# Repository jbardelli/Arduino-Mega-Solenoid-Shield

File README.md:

# Arduino-Mega-Solenoid-Shield
Kicad files for a solenoid valve driver shield compatible with Arduino Mega

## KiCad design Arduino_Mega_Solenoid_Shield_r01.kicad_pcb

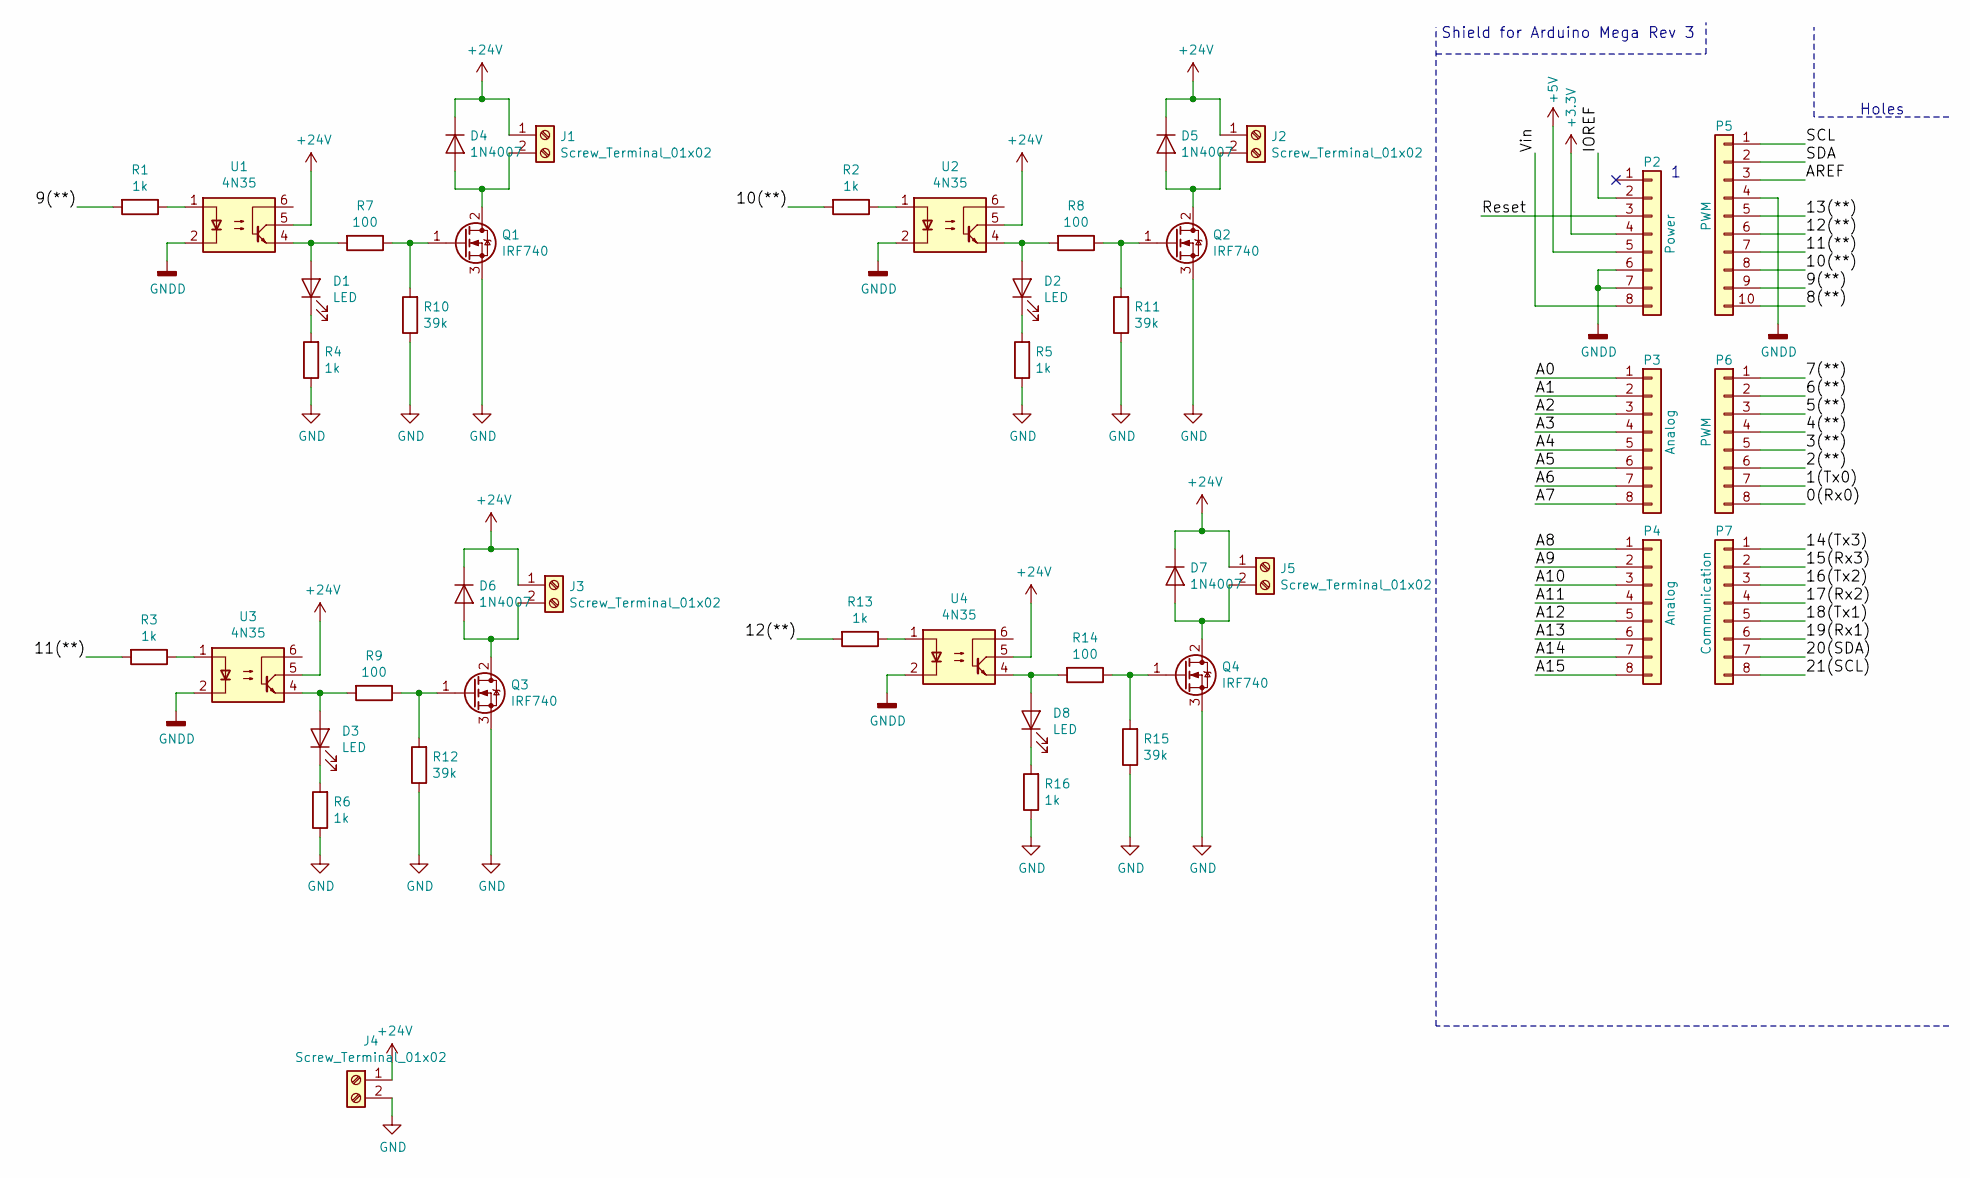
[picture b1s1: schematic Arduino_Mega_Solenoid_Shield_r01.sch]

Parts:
D1, D2, D3, D8: LED; LED_D3.0mm
D4, D5, D6, D7: 1N4007; D_DO-41_SOD81_P3.81mm_Vertical_KathodeUp
J1, J2, J3, J4, J5: Screw_Terminal_01x02; TerminalBlock_bornier-2_P5.08mm
P2: Power; Socket_Strip_Arduino_1x08
P3, P4: Analog; Socket_Strip_Arduino_1x08
P5: PWM; Socket_Strip_Arduino_1x10
P6: PWM; Socket_Strip_Arduino_1x08
P7: Communication; Socket_Strip_Arduino_1x08
Q1, Q2, Q3, Q4: IRF740; TO-220-3_Vertical
R1, R2, R3, R4, R5, R6, R13, R16: 1k; R_Axial_DIN0207_L6.3mm_D2.5mm_P7.62mm_Horizontal
R7, R8, R9, R14: 100; R_Axial_DIN0207_L6.3mm_D2.5mm_P7.62mm_Horizontal
R10, R11, R12, R15: 39k; R_Axial_DIN0207_L6.3mm_D2.5mm_P7.62mm_Horizontal
U1, U2, U3, U4: 4N35; DIP-6_W7.62mm

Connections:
+3V3: P2.4
+5V: P2.5
+24V: D4.1 (K), D5.1 (K), D6.1 (K), D7.1 (K), J1.1, J2.1, J3.1, J4.1, J5.1, U1.5, U2.5, U3.5, U4.5
/0(Rx0): P6.8
/1(Tx0): P6.7
/2(**): P6.6
/3(**): P6.5
/4(**): P6.4
/5(**): P6.3
/6(**): P6.2
/7(**): P6.1
/8(**): P5.10
/9(**): P5.9, R1.2
/10(**): P5.8, R2.2
/11(**): P5.7, R3.2
/12(**): P5.6, R13.2
/13(**): P5.5
/14(Tx3): P7.1
/15(Rx3): P7.2
/16(Tx2): P7.3
/17(Rx2): P7.4
/18(Tx1): P7.5
/19(Rx1): P7.6
/20(SDA): P7.7
/21(SCL): P7.8
/A0: P3.1
/A1: P3.2
/A2: P3.3
/A3: P3.4
/A4: P3.5
/A5: P3.6
/A6: P3.7
/A7: P3.8
/A8: P4.1
/A9: P4.2
/A10: P4.3
/A11: P4.4
/A12: P4.5
/A13: P4.6
/A14: P4.7
/A15: P4.8
/AREF: P5.3
/IOREF: P2.2
/Reset: P2.3
/SCL: P5.1
/SDA: P5.2
/Vin: P2.8
GND: J4.2, Q1.3 (S), Q2.3 (S), Q3.3 (S), Q4.3 (S), R4.1, R5.1, R6.1, R10.1, R11.1, R12.1, R15.1, R16.1
GNDD: P2.6, P2.7, P5.4, U1.2, U2.2, U3.2, U4.2
unnamed: D1.1 (K), R4.2
unnamed: D1.2 (A), R7.2, U1.4
unnamed: D2.1 (K), R5.2
unnamed: D2.2 (A), R8.2, U2.4
unnamed: D3.1 (K), R6.2
unnamed: D3.2 (A), R9.2, U3.4
unnamed: D4.2 (A), J1.2, Q1.2 (D)
unnamed: D5.2 (A), J2.2, Q2.2 (D)
unnamed: D6.2 (A), J3.2, Q3.2 (D)
unnamed: D7.2 (A), J5.2, Q4.2 (D)
unnamed: D8.1 (K), R16.2
unnamed: D8.2 (A), R14.2, U4.4
unnamed: Q1.1 (G), R7.1, R10.2
unnamed: Q2.1 (G), R8.1, R11.2
unnamed: Q3.1 (G), R9.1, R12.2
unnamed: Q4.1 (G), R14.1, R15.2
unnamed: R1.1, U1.1
unnamed: R2.1, U2.1
unnamed: R3.1, U3.1
unnamed: R13.1, U4.1

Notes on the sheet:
Shield for Arduino Mega Rev 3
Holes

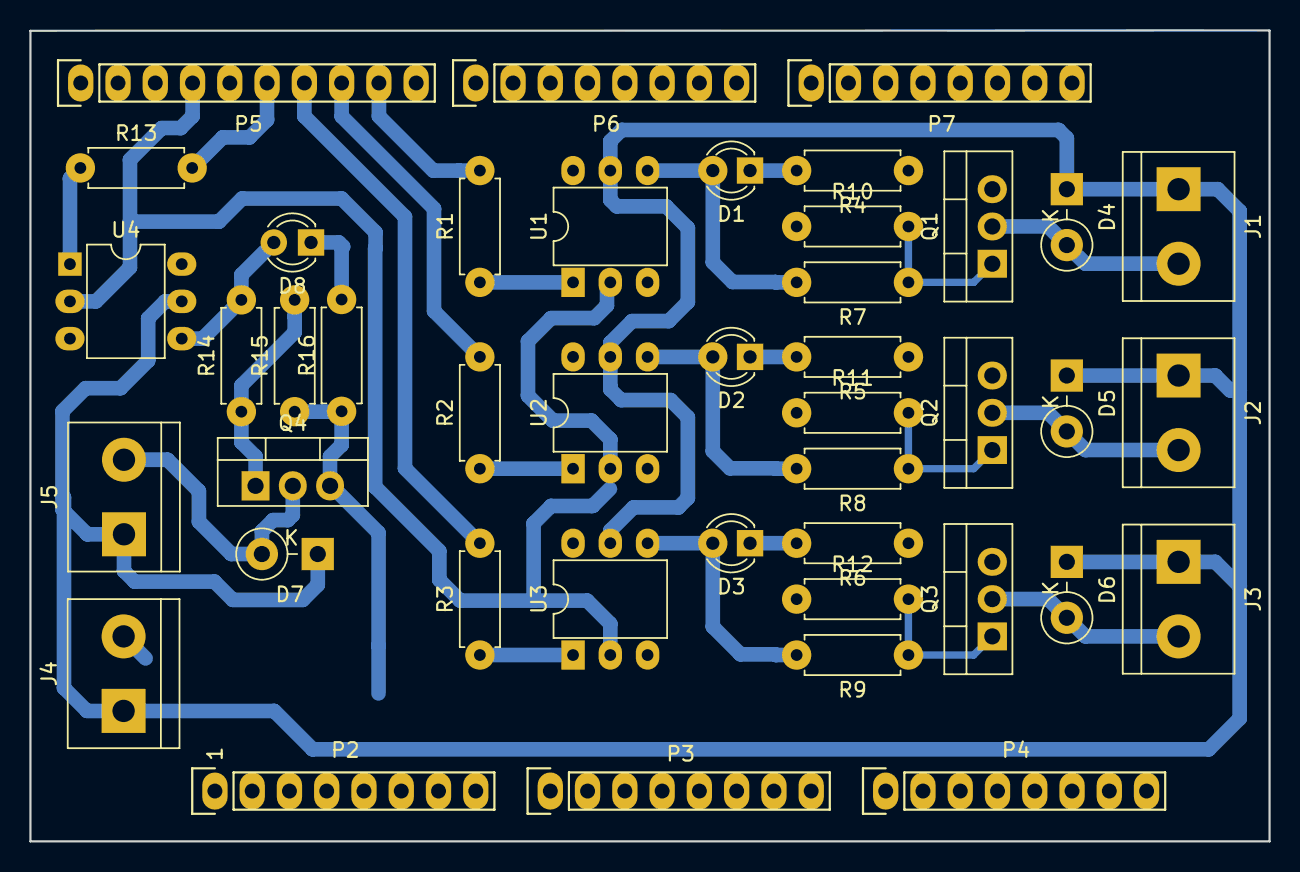
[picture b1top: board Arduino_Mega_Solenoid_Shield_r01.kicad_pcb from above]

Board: 2 copper layers, 84.5 x 55.3 mm, 43 parts (0 on the bottom side), 27 nets.

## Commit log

2021-05-19 Kicad files for Arduino Mega shield solenoid valve drivers
2021-05-19 Addes picture of the finished pcb.
2021-05-19 Picture of the finished solenoid valve shield
